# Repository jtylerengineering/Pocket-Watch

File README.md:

# Pocket-Watch

## Description

This is a digital Stopwatch powered with an ESP32 S3 using a 1.54" TFT Display. The Libraries used are **Adafruit GFX, ST7789, Time, and BLE**. The display also adjusts brightness to reduce eye-fatigue while using the pocket watch. 

## Requirements

### Components
Below is the list of needed components
| Part                      | Units | Unit Price | Total (parts) | Source Link                                                                                                                                                                                                                                                                                                                                                                                                                                                                                                                                                                                                                                                                                                                                                                                                                                                                                                                                                                                                                                                                                                                                                                                                                                                                                                                                                                                    |
|---------------------------|-------|------------|---------------|------------------------------------------------------------------------------------------------------------------------------------------------------------------------------------------------------------------------------------------------------------------------------------------------------------------------------------------------------------------------------------------------------------------------------------------------------------------------------------------------------------------------------------------------------------------------------------------------------------------------------------------------------------------------------------------------------------------------------------------------------------------------------------------------------------------------------------------------------------------------------------------------------------------------------------------------------------------------------------------------------------------------------------------------------------------------------------------------------------------------------------------------------------------------------------------------------------------------------------------------------------------------------------------------------------------------------------------------------------------------------------------------|
| 1.3" TFT Display          | 1     | $8.52      | 8.52          | https://www.aliexpress.us/item/3256808098235758.html?spm=a2g0o.cart.shoppingCartRecommend.11.71a438daiRIkV4&gps-id=shoppingCartRecommend&scm=1007.13440.426876.0&scm_id=1007.13440.426876.0&scm-url=1007.13440.426876.0&pvid=e62cf8d7-ca9c-42d5-a4e9-d63b1aebaa35&_t=gps-id%3AshoppingCartRecommend%2Cscm-url%3A1007.13440.426876.0%2Cpvid%3Ae62cf8d7-ca9c-42d5-a4e9-d63b1aebaa35%2Ctpp_buckets%3A668%232846%238110%231995&pdp_ext_f=%7B%22order%22%3A%221148%22%2C%22eval%22%3A%221%22%2C%22sceneId%22%3A%223440%22%2C%22fromPage%22%3A%22recommend%22%7D&pdp_npi=6%40dis%21USD%215.21%211.09%21%21%2134.58%217.24%21%402101c69517931338988076450e0d10%2112000044477900259%21rec%21US%218282019388%21ABXZ%211%210%21n_tag%3A-29910%3Bd%3A76ba61b4%3Bm03_new_user%3A-29895%3BpisId%3A5000000218165380&utparam-url=scene%3AshoppingCartRecommend%7Cquery_from%3A%7Cx_object_id%3A1005008284550510%7C_p_origin_prod%3A&_gl=1*1f3odxm*_gcl_aw*R0NMLjE3OTMwNTI2MjYuQ2p3S0NBanc5UHZXQmhBeEVpd0FkZHpZeVFLNlRTNW8yczdLVEVycDc4NU4tYjl3N0c4SFhuR2s1anBfWHEzSDBsb3hEWlNJblJNMFhSb0N6eklRQXZEX0J3RQ..*_gcl_dc*R0NMLjE3OTMwNTI2MjYuQ2p3S0NBanc5UHZXQmhBeEVpd0FkZHpZeVFLNlRTNW8yczdLVEVycDc4NU4tYjl3N0c4SFhuR2s1anBfWHEzSDBsb3hEWlNJblJNMFhSb0N6eklRQXZEX0J3RQ..*_gcl_au*NTU4NjE1ODIxLjE3OTI5NjU2NTA.*_ga*MjEzMzg5NTIwLjE3OTI5NzY2Mjk.*_ga_VED1YSGNC7*czE3OTMxNDIxMzQkbzYkZzAkdDE3OTMxNDIxMzQkajYwJGwwJGgw |
| Horizontal Rotary Encoder | 1     | $2.35      | $2.35         | https://www.aliexpress.us/item/3256806031729712.html?spm=a2g0o.detail.0.0.7b79F0mZF0mZpi&mp=1&pdp_npi=6%40dis%21USD%21USD+2.58%21USD+2.35%21%21USD+2.35%21%21%21%402101e80b17944431200736492e0f40%2112000036328342614%21ct%21US%218282019388%21%211%210%21&_gl=1*tlxsl4*_gcl_aw*R0NMLjE3OTQzNTI0MzguQ2owS0NRaUFuc3ZYQmhDcUFSSXNBSEtnR05hZENLMlRHdU5tSElUWkJyR1lBNnMwWjJFcVRJS2FRN2dtdnJhQnRkU0h3VzItblNWd3FCTWFBdEVIRUFMd193Y0I.*_gcl_dc*R0NMLjE3OTQzNTI0MzguQ2owS0NRaUFuc3ZYQmhDcUFSSXNBSEtnR05hZENLMlRHdU5tSElUWkJyR1lBNnMwWjJFcVRJS2FRN2dtdnJhQnRkU0h3VzItblNWd3FCTWFBdEVIRUFMd193Y0I.*_gcl_au*NTc0MTAzMTgxLjE3OTM4MzU4NTU.*_ga*MjEyNDg2ODk1MC4xNzkzODM1ODU1*_ga_VED1YSGNC7*czE3OTQ0NDI3NTUkbzYkZzEkdDE3OTQ0NDM5MzQkajQxJGwwJGgw&gatewayAdapt=glo2usa                                                                                                                                                                                                                                                                                                                                                                                                                                                                                                                                                                                                                                       |
| Xiao ESP32 S3             | 1     | $5.04      | $5.04         | https://www.aliexpress.us/item/3256809649066112.html?spm=a2g0o.productlist.main.8.6e8850c8m6OTJG&algo_pvid=940c728c-3a4c-4e7b-bcd2-af34709d51b5&aem_p4p_detail=2026110120351212482290581320340000010495&algo_exp_id=940c728c-3a4c-4e7b-bcd2-af34709d51b5-7&pdp_ext_f=%7B%22order%22%3A%22356%22%2C%22eval%22%3A%221%22%2C%22fromPage%22%3A%22search%22%7D&pdp_npi=6%40dis%21USD%215.05%211.09%21%21%2133.45%217.24%21%402103138417935941126154533e0f3d%2112000050316176722%21sea%21US%218282019388%21ABX%211%210%21n_tag%3A-29910%3Bd%3Accb82ee9%3Bm03_new_user%3A-29895%3BpisId%3A5000000218165391&curPageLogUid=sv0yhJZE7dbT&utparam-url=scene%3Asearch%7Cquery_from%3A%7Cx_object_id%3A1005009835380864%7C_p_origin_prod%3A&search_p4p_id=2026110120351212482290581320340000010495_2                                                                                                                                                                                                                                                                                                                                                                                                                                                                                                                                                                                                        |
| 100 mAh LiPO battery      | 1     | $8.78      | $8.78         | https://www.aliexpress.us/item/3256812815921486.html?spm=a2g0o.detail.0.0.69dbLuHgLuHglj&mp=1&pdp_npi=6%40dis%21USD%21USD+8.79%21USD+4.05%21%21USD+4.05%21%21%21%402103094f17944438611858550e0d3a%2112000059969109360%21ct%21US%218282019388%21%211%210%21&_gl=1*icwiu7*_gcl_aw*R0NMLjE3OTQzNTI0MzguQ2owS0NRaUFuc3ZYQmhDcUFSSXNBSEtnR05hZENLMlRHdU5tSElUWkJyR1lBNnMwWjJFcVRJS2FRN2dtdnJhQnRkU0h3VzItblNWd3FCTWFBdEVIRUFMd193Y0I.*_gcl_dc*R0NMLjE3OTQzNTI0MzguQ2owS0NRaUFuc3ZYQmhDcUFSSXNBSEtnR05hZENLMlRHdU5tSElUWkJyR1lBNnMwWjJFcVRJS2FRN2dtdnJhQnRkU0h3VzItblNWd3FCTWFBdEVIRUFMd193Y0I.*_gcl_au*NTc0MTAzMTgxLjE3OTM4MzU4NTU.*_ga*MjEyNDg2ODk1MC4xNzkzODM1ODU1*_ga_VED1YSGNC7*czE3OTQ0NDI3NTUkbzYkZzEkdDE3OTQ0NDM4NjAkajUzJGwwJGgw&gatewayAdapt=glo2usa                                                                                                                                                                                                                                                                                                                                                                                                                                                                                                                                                                                                                                       |
| capacitor                 | 1     | $1.86      | $1.86         | https://www.aliexpress.us/item/3256808297676167.html?spm=a2g0o.productlist.main.3.6cbd2eddpPff70&algo_pvid=dce21b81-690c-4665-b43c-6b3c196c6d04&algo_exp_id=dce21b81-690c-4665-b43c-6b3c196c6d04-2&pdp_ext_f=%7B%22order%22%3A%223134%22%2C%22eval%22%3A%221%22%2C%22fromPage%22%3A%22search%22%7D&pdp_npi=6%40dis%21USD%211.61%211.09%21%21%2110.71%217.23%21%402101c68a17944438523894418e0e44%2112000045347461237%21sea%21US%218282019388%21ABX%211%210%21n_tag%3A-29910%3Bd%3A601afdd8%3Bm03_new_user%3A-29895%3BpisId%3A5000000218165384&curPageLogUid=ATcJOr6FcXjK&utparam-url=scene%3Asearch%7Cquery_from%3A%7Cx_object_id%3A1005008483990919%7C_p_origin_prod%3A                                                                                                                                                                                                                                                                                                                                                                                                                                                                                                                                                                                                                                                                                                                        |
| PCB                       | 1     | $3.30      | $3.30         | https://jlcone.com/download                                                                                                                                                                                                                                                                                                                                                                                                                                                                                                                                                                                                                                                                                                                                                                                                                                                                                                                                                                                                                                                                                                                                                                                                                                                                                                                                                                    |
| Photoresistor             | 1     | $4.92      | $4.92         | https://www.aliexpress.us/item/3256811448721255.html?spm=a2g0o.productlist.main.5.520951a6SoY7ND&algo_pvid=722a7f46-b7b5-40f1-900d-3d523d1676b5&algo_exp_id=722a7f46-b7b5-40f1-900d-3d523d1676b5-4&pdp_ext_f=%7B%22order%22%3A%2246%22%2C%22eval%22%3A%221%22%2C%22fromPage%22%3A%22search%22%7D&pdp_npi=6%40dis%21USD%214.92%211.09%21%21%2132.69%217.26%21%402101e81117944436231992440e10f8%2112000056114133901%21sea%21US%218282019388%21ABX%211%210%21n_tag%3A-29910%3Bd%3A601afdd8%3Bm03_new_user%3A-29895%3BpisId%3A5000000218165389&curPageLogUid=g9nMcHm775dy&utparam-url=scene%3Asearch%7Cquery_from%3A%7Cx_object_id%3A1005011635036007%7C_p_origin_prod%3A                                                                                                                                                                                                                                                                                                                                                                                                                                                                                                                                                                                                                                                                                                                          |
| 330 Ohm Resistor          | 1     | $13.80     | $13.80        | https://www.aliexpress.us/item/3256812141299051.html?spm=a2g0o.productlist.main.2.26b32180A9kBVb&algo_pvid=db2a5d06-9d0a-4753-9625-0865c3fc25b6&algo_exp_id=db2a5d06-9d0a-4753-9625-0865c3fc25b6-1&pdp_ext_f=%7B%22order%22%3A%2246%22%2C%22eval%22%3A%221%22%2C%22fromPage%22%3A%22search%22%7D&pdp_npi=6%40dis%21USD%216.25%211.09%21%21%2141.49%217.22%21%402101e56817944437141364033e0e89%2112000058091527849%21sea%21US%218282019388%21ABX%211%210%21n_tag%3A-29910%3Bd%3A601afdd8%3Bm03_new_user%3A-29895%3BpisId%3A5000000218165391&curPageLogUid=uoCBaolbfTFi&utparam-url=scene%3Asearch%7Cquery_from%3A%7Cx_object_id%3A1005012327613803%7C_p_origin_prod%3A                                                                                                                                                                                                                                                                                                                                                                                                                                                                                                                                                                                                                                                                                                                          |
| Shipping                  |       | $5.30      |               |                                                                                                                                                                                                                                                                                                                                                                                                                                                                                                                                                                                                                                                                                                                                                                                                                                                                                                                                                                                                                                                                                                                                                                                                                                                                                                                                                                                                |
| Total                     |       | 53.87      |               |                                                                                                                                                                                                                                                                                                                                                                                                                                                                                                                                                                                                                                                                                                                                                                                                                                                                                                                                                                                                                                                                                                                                                                                                                                                                                                                                                                                                |

### Software
You will also need the Firmware file along with <a href="https://docs.arduino.cc/software/ide/">Arduino IDE</a>. 

#### Libraries
The necessary libraries to install are the <a href="https://github.com/adafruit/adafruit-gfx-library">Adafruit GFX Library</a>, the <a href="https://docs.arduino.cc/libraries/adafruit-st7735-and-st7789-library/">ST7789 Display Library</a>, and the <a href="https://docs.arduino.cc/libraries/esp32-ble-arduino/">ESP32 BLE Library</a>.

## Assembly

A set of assembly instructions will be committed during week 9, as to prevent misinformation and fix any discovered bugs.

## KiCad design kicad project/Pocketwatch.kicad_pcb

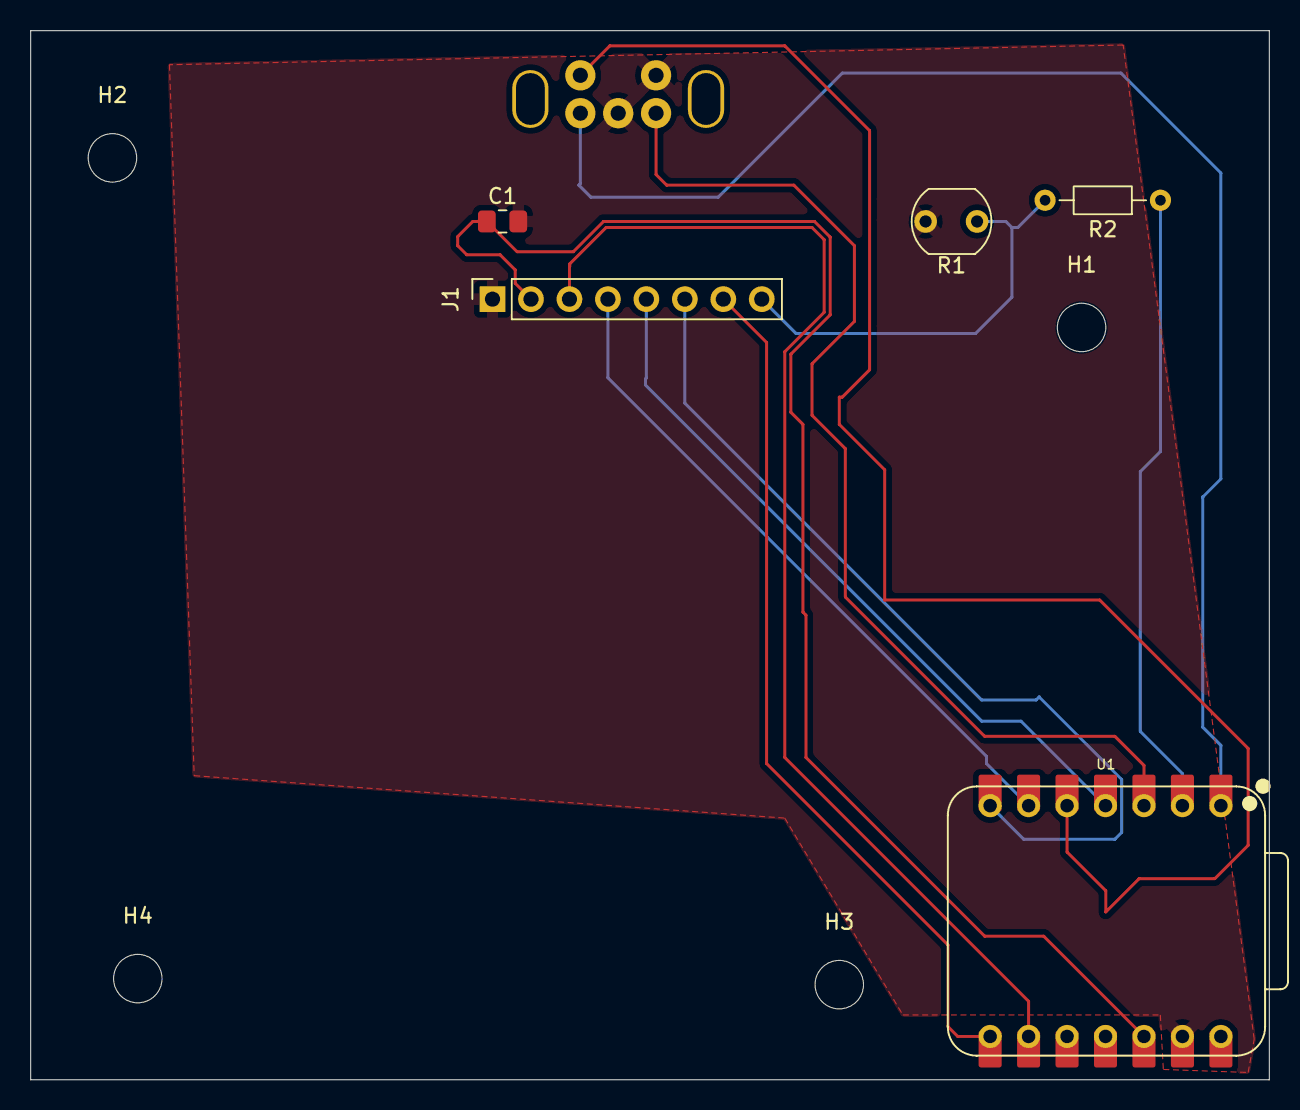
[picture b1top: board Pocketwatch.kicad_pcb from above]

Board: 2 copper layers, 81.8 x 69.3 mm, 10 parts (0 on the bottom side), 12 nets.

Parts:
C1: C_Small; C_0805_2012Metric_Pad1.18x1.45mm_HandSolder
H1, H2, H3, H4: MountingHole; MountingHole_3.2mm_M3
J1: Conn_01x08_Socket; PinSocket_1x08_P2.54mm_Vertical
R1: R_Photo; R_LDR_5.1x4.3mm_P3.4mm_Vertical
R2: R_US; R_Axial_DIN0204_L3.6mm_D1.6mm_P7.62mm_Horizontal
SW1: RotaryEncoder_Switch; RotaryEncoder_EC11B-Horizontal-Dual
U1: XIAO-ESP32-S3-SMD; XIAO-ESP32-S3-DIP

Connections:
+3.3V: C1.1, J1.2, U1.12 (3V3_OUT)
/BL: R2.1, U1.2 (D1)
/CS: J1.7, U1.8 (D7)
/DC: J1.6, U1.7 (D6)
/En_SW: SW1.S1, U1.5 (D4)
/RST: J1.5, U1.4 (D3)
/Rot A: SW1.A, U1.1 (D0)
/Rot B: SW1.B, U1.3 (D2)
/SCL: J1.3, U1.9 (D8)
/SDA: J1.4, U1.6 (D5)
GND: C1.2, J1.1, R1.2, SW1.C, SW1.S2, U1.13 (GND)
unnamed: J1.8, R1.1, R2.2
